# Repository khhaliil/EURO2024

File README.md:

# EURO2024

Mar7bé bikom lel repository mta3 Project EURO2024! Hetha el document besh y'awnek kifech ta3mel contribution lel different directories mta3 el project.

## Structure mta3 el Repository

El repository m3abbi b'bezdet directories, kol wa7ed menhom mechi ykoun corresponding lel jihet spécifique mta3 el project:

- Communication
- Documentation
- Electronique
- Mecanique
- Test
- Tools
- Vision

Kol directory andha el team mta3ha li mas2oul 3liha.

## Kifech Ta3mel Contribution

Besh tcontribute lel repository, please suivez hethom lé étapes:

### Kifech Ta3mel Setup l Workspace mta3ek

1. **Clone el Repository**:
   - Clone el repository lel machine mta3ek b'using:
     ```sh
     git clone https://github.com/khhaliil/EURO204.git
     ```
   - Emchi lel directory eli clonitou:
     ```sh
     cd repo-name
     ```

### Kifech Ta3mel Contributions

2. **Create a New Branch lel khedma mta3ek**:
   - Avant ma ta3mel ay changes, create a new branch men `main`:
     ```sh
     git checkout -b your-feature-branch
     ```
   - Badel `your-feature-branch` b'esm descriptive lel branch mta3ek (par exemple, `vision-enhancements`).

3. **A3mel el Changes mta3ek**:
   - A3mel el changes mté3ek f'dakhal el directory li inti mas2oul 3liha.
   - T'hebb t'koun sur belli suiveit el README template li mawjoud lel kol directory.

4. **Committing el Changes**:
   - Après ma ta3mel el changes, stage your changes lel commit:
     ```sh
     git add .
     ```
   - Commit el changes mta3ek b'message descriptive:
     ```sh
     git commit -m "Add a concise, descriptive comment about your changes"
     ```

5. **Pushing el Changes**:
   - Push el branch lel remote repository:
     ```sh
     git push origin your-feature-branch
     ```

### Kifech Ta3mel Pull Request

6. **Emchi lel Pull Request (PR)**:
   - Emchi lel repository 3la GitHub.
   - Clique 3la "Pull request" button.
   - Chouz el branch mta3ek w provide a clear description lel changes.

7. **Code Review**:
   - Talab review men teammate ou min maintainer.
   - Jaweb 3la ay feedback w dir ay changes necessary.

8. **Merging lel Main**:
   - Lamma el PR ti7dher, it can be merged into el `main` branch.

### Kifech Tjadded Changes

9. **Stay Updated**:
   - Besh t'koun daima updated, regularly pull changes men el `main` branch:
     ```sh
     git checkout main
     git pull origin main
     ```

# README Template lel Directories

Kol directory lazmha tkoun fih README b'hal structure:

```markdown
# Essem el Directory

## Overview

Description breve kifech hetha el directory fih o shnuwa purpose mta3ou fel project.

## Structure

- `essem_file_ou_subdirectory` - Description lel contenu ou subdirectory.

## Setup and Installation

Ay setup steps ou instructions d'installation mte3bin spécifiquement lel directory hetha.

## Usage

Instructions kifech tista3mel el modules ou tools eli fih el directory.

## Contributing

Guidelines spécifiques lel contribution lel directory hetha, ila kayen.

## Contact

Mén contacti besh tassa2el 3la queries related lel directory.
```

Copy w paste hetha el template f'koll README.md lel kol directory w updateih b'el information relevant.

--- 

As before, replace "your-org/EURO204.git" and "repo-name" with your actual organization and repository names, and update any other placeholders as necessary.

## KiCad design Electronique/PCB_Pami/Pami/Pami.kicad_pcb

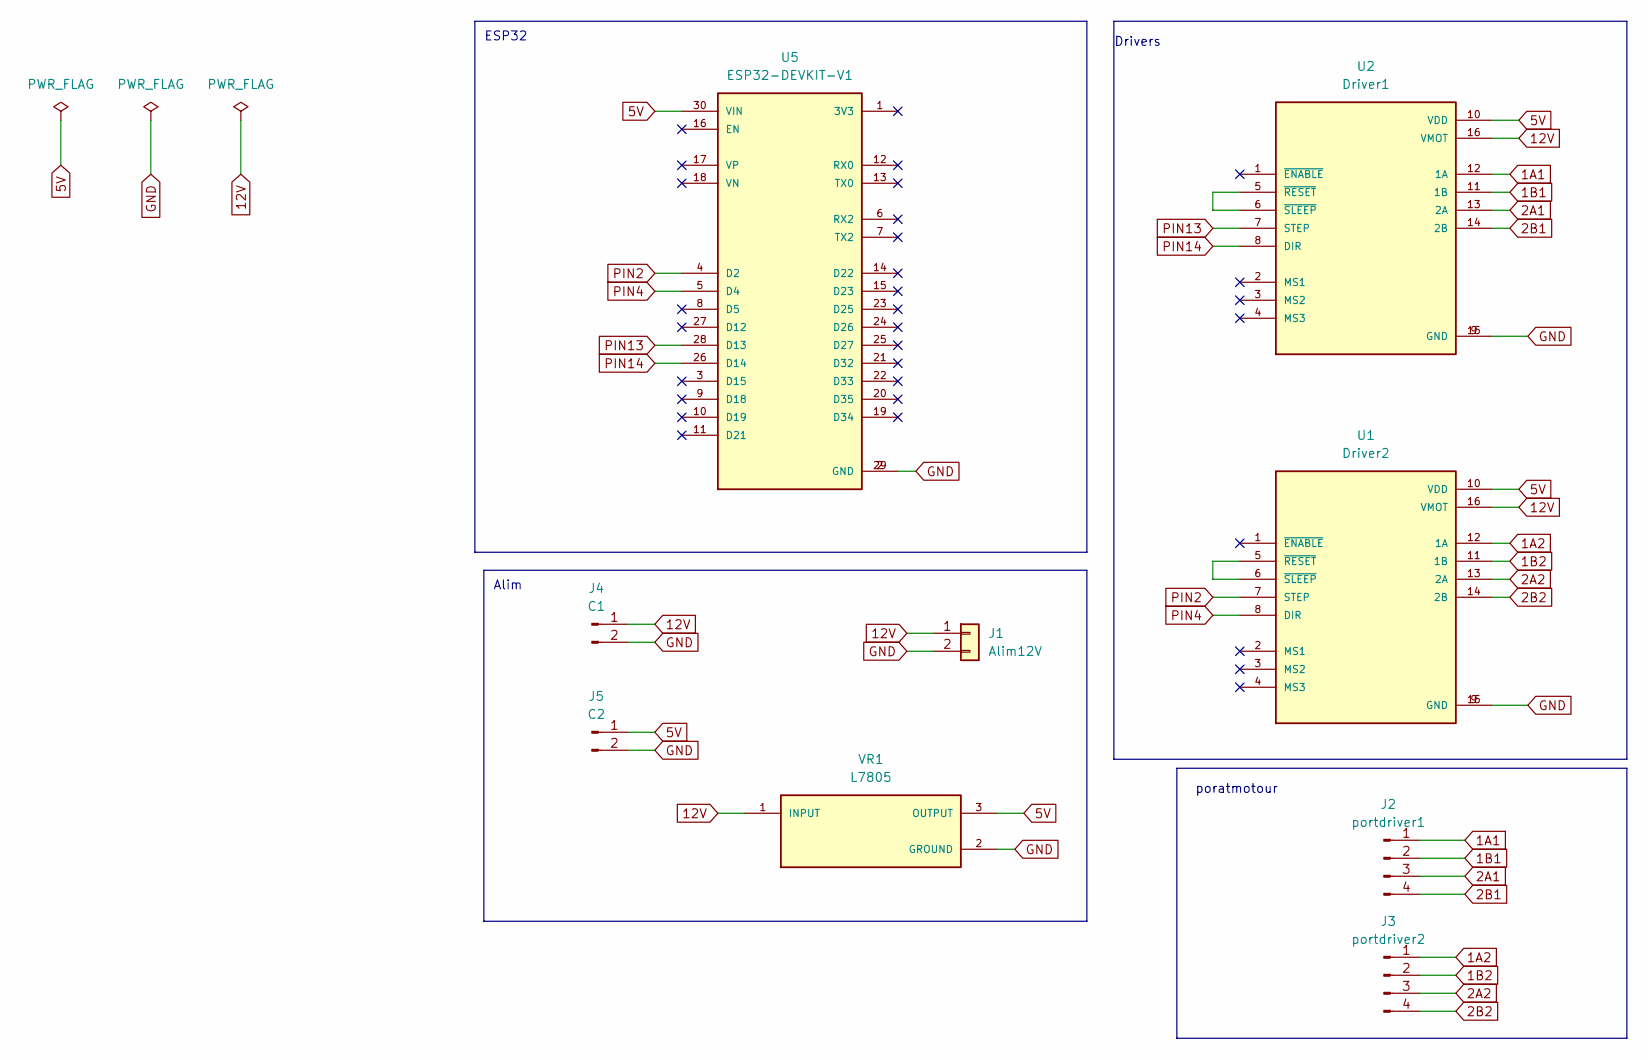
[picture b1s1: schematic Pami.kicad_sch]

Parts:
J1: Alim12V; PinHeader_1x02_P2.54mm_Vertical
J2: portdriver1; PinHeader_1x04_P2.00mm_Vertical
J3: portdriver2; PinHeader_1x04_P2.00mm_Vertical
J4: C1; PinHeader_1x02_P2.54mm_Vertical
J5: C2; PinHeader_1x02_P2.54mm_Vertical
U1: Driver2; MODULE_A4988_STEPPER_MOTOR_DRIVER_CARRIER
U2: Driver1; MODULE_A4988_STEPPER_MOTOR_DRIVER_CARRIER
U5: ESP32-DEVKIT-V1; MODULE_ESP32_DEVKIT_V1; PARTREV N/A
VR1: L7805; TO255P1020X450X2000-3; PARTREV 36

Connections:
1A1: J2.1, U2.12 (1A)
1A2: J3.1, U1.12 (1A)
1B1: J2.2, U2.11 (1B)
1B2: J3.2, U1.11 (1B)
2A1: J2.3, U2.13 (2A)
2A2: J3.3, U1.13 (2A)
2B1: J2.4, U2.14 (2B)
2B2: J3.4, U1.14 (2B)
5V: J5.1, U1.10 (VDD), U2.10 (VDD), U5.30 (VIN), VR1.3 (OUTPUT)
12V: J1.1, J4.1, U1.16 (VMOT), U2.16 (VMOT), VR1.1 (INPUT)
GND: J1.2, J4.2, J5.2, U1.9 (GND), U1.15 (GND), U2.9 (GND), U2.15 (GND), U5.2 (GND), U5.29 (GND), VR1.2 (GROUND)
unnamed: U1.5 (~RESET), U1.6 (~SLEEP)
unnamed: U2.5 (~RESET), U2.6 (~SLEEP)
PIN2: U1.7 (STEP), U5.4 (D2)
PIN4: U1.8 (DIR), U5.5 (D4)
PIN13: U2.7 (STEP), U5.28 (D13)
PIN14: U2.8 (DIR), U5.26 (D14)

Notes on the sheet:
Drivers
Alim
poratmotour
ESP32

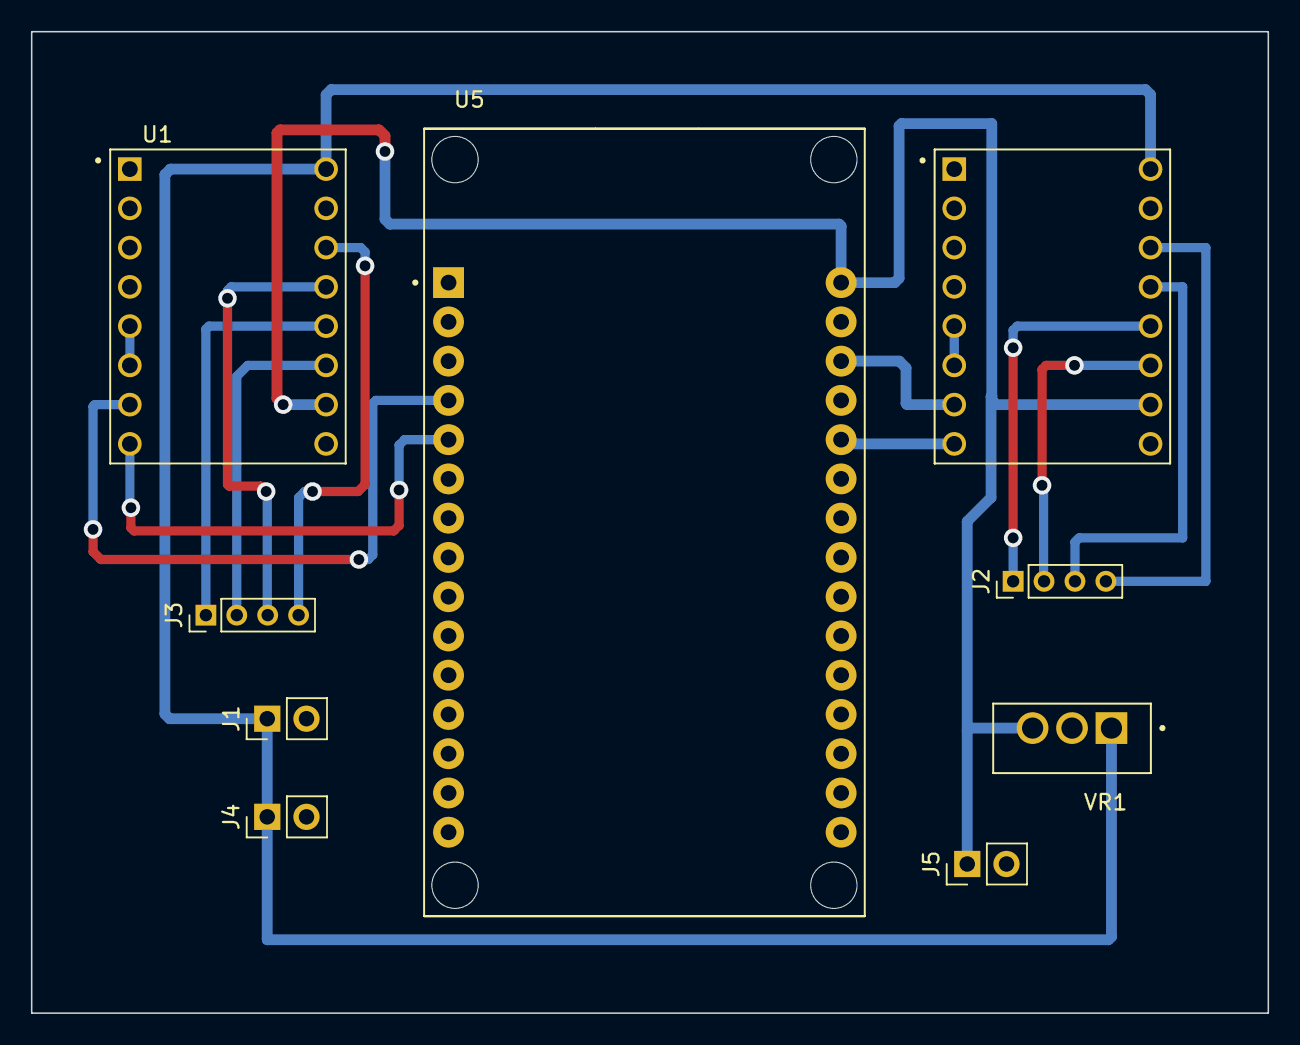
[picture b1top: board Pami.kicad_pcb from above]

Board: 2 copper layers, 80.0 x 63.5 mm, 9 parts (0 on the bottom side), 17 nets.

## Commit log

2023-11-22 structure
2023-11-22 init
2023-11-22 struc
2023-11-24 calibration
    ajout d'un code pour calibrer la camera
2023-11-26 settiing up directories for Gazebo simulation
2023-11-26 how to .md
2023-11-26 arbi.md
2023-11-27 Pami
2023-11-28 test
    rahi test
2023-11-28 prepapration
    wrote the world.xml file that describes the world (from a basic exemple video) , set up the CmakeList file and the package
2023-11-28 prep
2023-12-01 Test Pami
    V0
2023-12-03 aruco code detection with 3 cameras and stacking
2023-12-03 denoising
2023-12-03 calibration test
2023-12-03 transformation using mouse clicks + calibration matrix for the macro cam
2023-12-04 Distance estimation
    need calibration for the micrsoft camera
    need generalasation for the 3 cams
    need to change the location folder of .npz output file
2023-12-04 updated the ignore
    removed Euro_venv
2023-12-04 update of the 3 cams
2023-12-05 init ROS by Karim
2023-12-05 added calibration for the microsoft camera
2023-12-05 updated the ignore so it ignores the png files
2023-12-05 Update gitignore
2023-12-09 top down view completion
    - added both calib matrixes for Xiaomi 0.5 lens / Xiaomi normal lens
    - added capturing Chessboard calibration Images from a presaved MP4 video
    - capture_images_chesboard is adpated to save automatically each x seconds without the need to click on S
    - detect Aruco code is to get a feeling , it detects withou mouse 4 clicks then performs a top down view
    - PnP try is the Code that tranforms everything it takes an img and returns a top down view
2023-12-12 video stream instead of single image
    topdownview is a modular try for the pnp_try code
2023-12-23 starting my branch with euro team
2023-12-27 updating my work
2023-12-27 done
2024-01-13 tweaking for the new map
    - marker length
    - marker x,y positions
    - flipped the camera cuz i was filming upsidesown
2024-01-13 renamed the file
2024-01-13 saving + calibration
2024-01-16 updates and major changes
    optimsed the main
    added pixel to mm
    added homography function
    added saving
    added kalman filtering
2024-01-17 tweaking main
2024-01-17 update
    kalman trcking
2024-01-17 updating the safety_distance
2024-01-18 testing
2024-01-19 modele v0
2024-01-19 updating my RRT code
2024-01-19 updating the testRRT main file
2024-01-19 updating more and more
2024-01-19 updated the model
2024-01-25 update distorsion of centers
2024-01-25 PCB_Pami
2024-01-25 updating, updating and updating
2024-01-28 testing some cases
2024-01-28 run another model saved in runs modele v1.1 train 11
    another model
    cleaned some code
    distorsion correction of the center of the bounding boxes
2024-01-29 updated directories
2024-02-13 newest
2024-02-19 Navigation Main Robot f407
    Check point
2024-02-19 nav newest 2/19
    take only whats necessary
2024-02-20 navigation
2024-02-29 adding the adverse dim
2024-02-29 ypdating testRRT.py
2024-03-05 updating the code so we can change our robot radius
2024-03-22 dynamic alloc
